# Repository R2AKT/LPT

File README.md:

License addendum - https://github.com/R2AKT/LPT/blob/main/Addendum.txt

# LPT

LPT (Centrinics) module. For Mega-80 (Mega-580) DIY 8-bit micro-computer - https://github.com/R2AKT/Mega-80.

Based on 82C11 (1834VV11).

Status: In production. Not tested.

Модуль LPT (Centrinics). Для самодельной 8-битной микро-ЭВМ - https://github.com/R2AKT/Mega-80.

На основе 1834ВВ11 (82C11).

Статус: Изготовливается. Не тестировалась.

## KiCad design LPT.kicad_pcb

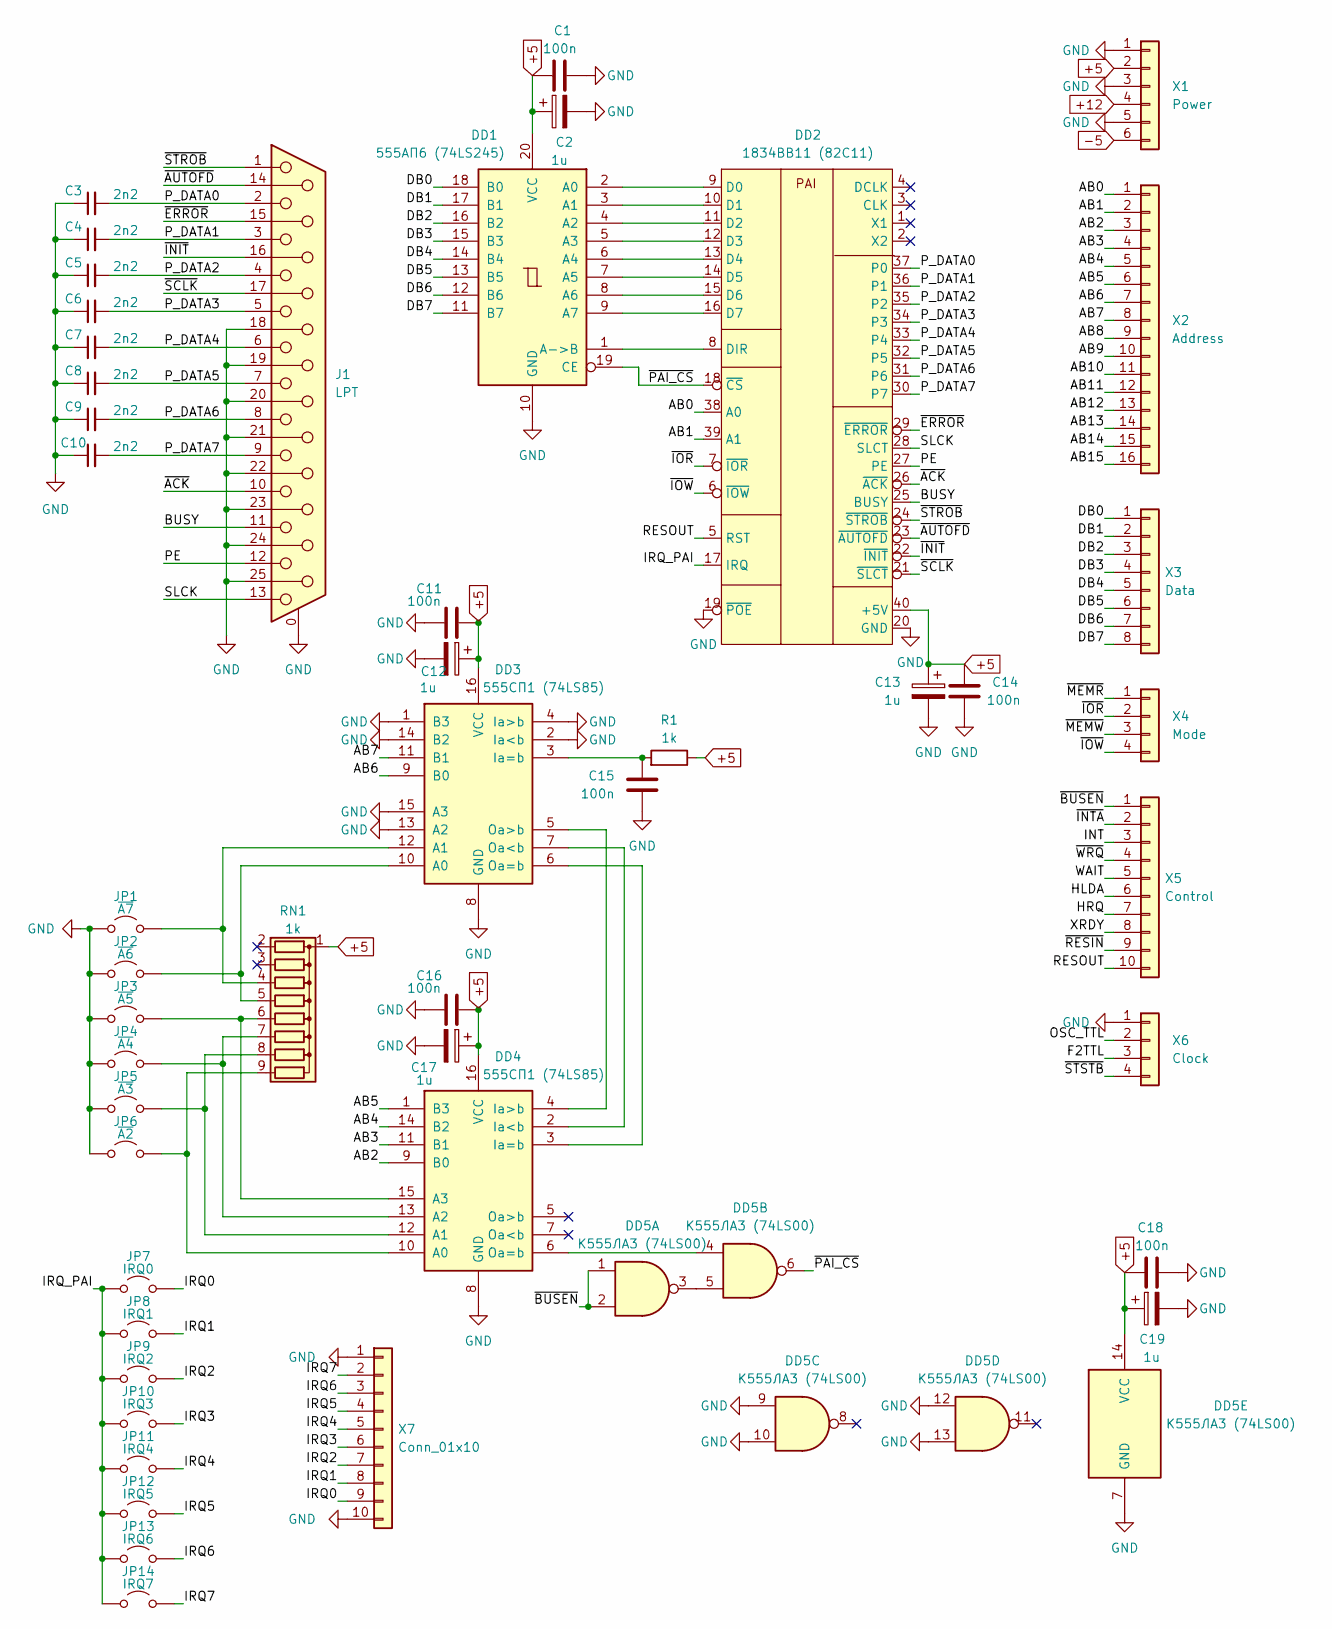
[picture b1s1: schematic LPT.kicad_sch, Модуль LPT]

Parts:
C1, C11, C14, C15, C16, C18: 100n; C_0805_2012Metric_Pad1.18x1.45mm_HandSolder
C2, C12, C13, C17, C19: 1u; CP_EIA-3216-18_Kemet-A_Pad1.58x1.35mm_HandSolder
C3, C4, C5, C6, C7, C8, C9, C10: 2n2; C_0805_2012Metric_Pad1.18x1.45mm_HandSolder
DD1: 555АП6 (74LS245); DIP-20_W7.62mm_Socket_LongPads
DD2: 1834ВВ11 (82C11); DIP-40_W15.24mm_Socket_LongPads
DD3, DD4: 555СП1 (74LS85); DIP-16_W7.62mm_Socket_LongPads
DD5: К555ЛА3 (74LS00); DIP-14_W7.62mm_Socket_LongPads
J1: LPT; DSUB-25_Female_Horizontal_P2.77x2.84mm_EdgePinOffset7.70mm_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
JP1: ~{A7}; SolderJumper-2_P1.3mm_Open_RoundedPad1.0x1.5mm
JP2: ~{A6}; SolderJumper-2_P1.3mm_Open_RoundedPad1.0x1.5mm
JP3: ~{A5}; SolderJumper-2_P1.3mm_Open_RoundedPad1.0x1.5mm
JP4: ~{A4}; SolderJumper-2_P1.3mm_Open_RoundedPad1.0x1.5mm
JP5: ~{A3}; SolderJumper-2_P1.3mm_Open_RoundedPad1.0x1.5mm
JP6: ~{A2}; SolderJumper-2_P1.3mm_Open_RoundedPad1.0x1.5mm
JP7: IRQ0; SolderJumper-2_P1.3mm_Open_RoundedPad1.0x1.5mm
JP8: IRQ1; SolderJumper-2_P1.3mm_Open_RoundedPad1.0x1.5mm
JP9: IRQ2; SolderJumper-2_P1.3mm_Open_RoundedPad1.0x1.5mm
JP10: IRQ3; SolderJumper-2_P1.3mm_Open_RoundedPad1.0x1.5mm
JP11: IRQ4; SolderJumper-2_P1.3mm_Open_RoundedPad1.0x1.5mm
JP12: IRQ5; SolderJumper-2_P1.3mm_Open_RoundedPad1.0x1.5mm
JP13: IRQ6; SolderJumper-2_P1.3mm_Open_RoundedPad1.0x1.5mm
JP14: IRQ7; SolderJumper-2_P1.3mm_Open_RoundedPad1.0x1.5mm
R1: 1k; R_0805_2012Metric_Pad1.20x1.40mm_HandSolder
RN1: 1k; R_Array_SIP9
X1: Power; PinHeader_1x06_P2.54mm_Vertical
X2: Address; PinHeader_1x16_P2.54mm_Vertical
X3: Data; PinHeader_1x08_P2.54mm_Vertical
X4: Mode; PinHeader_1x04_P2.54mm_Vertical
X5: Control; PinHeader_1x10_P2.54mm_Vertical
X6: Clock; PinHeader_1x04_P2.54mm_Vertical
X7: Conn_01x10; PinHeader_1x10_P2.54mm_Vertical

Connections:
+5: C1.1, C2.1, C11.1, C12.1, C13.1, C14.1, C16.1, C17.1, C18.1, C19.1, DD1.20 (VCC), DD2.40 (+5V), DD3.16 (VCC), DD4.16 (VCC), DD5.14 (VCC), R1.1, RN1.1 (common), X1.2
+12: X1.4
-5: X1.6
/AB0: DD2.38 (A0), X2.1
/AB1: DD2.39 (A1), X2.2
/AB2: DD4.9 (B0), X2.3
/AB3: DD4.11 (B1), X2.4
/AB4: DD4.14 (B2), X2.5
/AB5: DD4.1 (B3), X2.6
/AB6: DD3.9 (B0), X2.7
/AB7: DD3.11 (B1), X2.8
/AB8: X2.9
/AB9: X2.10
/AB10: X2.11
/AB11: X2.12
/AB12: X2.13
/AB13: X2.14
/AB14: X2.15
/AB15: X2.16
/BUSY: DD2.25 (BUSY), J1.11
/DB0: DD1.18 (B0), X3.1
/DB1: DD1.17 (B1), X3.2
/DB2: DD1.16 (B2), X3.3
/DB3: DD1.15 (B3), X3.4
/DB4: DD1.14 (B4), X3.5
/DB5: DD1.13 (B5), X3.6
/DB6: DD1.12 (B6), X3.7
/DB7: DD1.11 (B7), X3.8
/F2TTL: X6.3
/HLDA: X5.6
/HRQ: X5.7
/INT: X5.3
/IRQ0: JP7.2 (B), X7.9
/IRQ1: JP8.2 (B), X7.8
/IRQ2: JP9.2 (B), X7.7
/IRQ3: JP10.2 (B), X7.6
/IRQ4: JP11.2 (B), X7.5
/IRQ5: JP12.2 (B), X7.4
/IRQ6: JP13.2 (B), X7.3
/IRQ7: JP14.2 (B), X7.2
/IRQ_PAI: DD2.17 (IRQ), JP7.1 (A), JP8.1 (A), JP9.1 (A), JP10.1 (A), JP11.1 (A), JP12.1 (A), JP13.1 (A), JP14.1 (A)
/OSC_TTL: X6.2
/PE: DD2.27 (PE), J1.12
/P_DATA0: C3.2, DD2.37 (P0), J1.2
/P_DATA1: C4.2, DD2.36 (P1), J1.3
/P_DATA2: C5.2, DD2.35 (P2), J1.4
/P_DATA3: C6.2, DD2.34 (P3), J1.5
/P_DATA4: C7.2, DD2.33 (P4), J1.6
/P_DATA5: C8.2, DD2.32 (P5), J1.7
/P_DATA6: C9.2, DD2.31 (P6), J1.8
/P_DATA7: C10.2, DD2.30 (P7), J1.9
/RESOUT: DD2.5 (RST), X5.10
/SLCK: DD2.28 (SLCT), J1.13
/WAIT: X5.5
/XRDY: X5.8
/~ACK: DD2.26 (~ACK), J1.10
/~AUTOFD: DD2.23 (~AUTOFD), J1.14
/~BUSEN: DD5.1, DD5.2, X5.1
/~ERROR: DD2.29 (~ERROR), J1.15
/~INIT: DD2.22 (~INIT), J1.16
/~INTA: X5.2
/~IOR: DD2.7 (~IOR), X4.2
/~IOW: DD2.6 (~IOW), X4.4
/~MEMR: X4.1
/~MEMW: X4.3
/~PAI_CS: DD1.19 (CE), DD2.18 (~CS), DD5.6
/~RESIN: X5.9
/~SCLK: DD2.21 (~SLCT), J1.17
/~STROB: DD2.24 (~STROB), J1.1
/~STSTB: X6.4
/~WRQ: X5.4
GND: C1.2, C2.2, C3.1, C4.1, C5.1, C6.1, C7.1, C8.1, C9.1, C10.1, C11.2, C12.2, C13.2, C14.2, C15.2, C16.2, C17.2, C18.2, C19.2, DD1.10 (GND), DD2.19 (~POE), DD2.20 (GND), DD3.1 (B3), DD3.2 (Ia<b), DD3.4 (Ia>b), DD3.8 (GND), DD3.13 (A2), DD3.14 (B2), DD3.15 (A3), DD4.8 (GND), DD5.7 (GND), DD5.9, DD5.10, DD5.12, DD5.13, J1.0 (PAD), J1.18, J1.19, J1.20, J1.21, J1.22, J1.23, J1.24, J1.25, JP1.1 (A), JP2.1 (A), JP3.1 (A), JP4.1 (A), JP5.1 (A), JP6.1 (A), X1.1, X1.3, X1.5, X6.1, X7.1, X7.10
unnamed: DD1.2 (A0), DD2.9 (D0)
unnamed: DD1.3 (A1), DD2.10 (D1)
unnamed: DD1.4 (A2), DD2.11 (D2)
unnamed: DD1.5 (A3), DD2.12 (D3)
unnamed: DD1.6 (A4), DD2.13 (D4)
unnamed: DD1.7 (A5), DD2.14 (D5)
unnamed: DD1.8 (A6), DD2.15 (D6)
unnamed: DD1.9 (A7), DD2.16 (D7)
unnamed: DD1.1 (A->B), DD2.8 (DIR)
unnamed: DD3.10 (A0), JP2.2 (B), RN1.5 (R4)
unnamed: DD3.12 (A1), JP1.2 (B), RN1.4 (R3)
unnamed: C15.1, DD3.3 (Ia=b), R1.2
unnamed: DD3.7 (Oa<b), DD4.2 (Ia<b)
unnamed: DD3.6 (Oa=b), DD4.3 (Ia=b)
unnamed: DD3.5 (Oa>b), DD4.4 (Ia>b)
unnamed: DD4.10 (A0), JP6.2 (B), RN1.9 (R8)
unnamed: DD4.12 (A1), JP5.2 (B), RN1.8 (R7)
unnamed: DD4.13 (A2), JP4.2 (B), RN1.7 (R6)
unnamed: DD4.15 (A3), JP3.2 (B), RN1.6 (R5)
unnamed: DD4.6 (Oa=b), DD5.4
unnamed: DD5.3, DD5.5

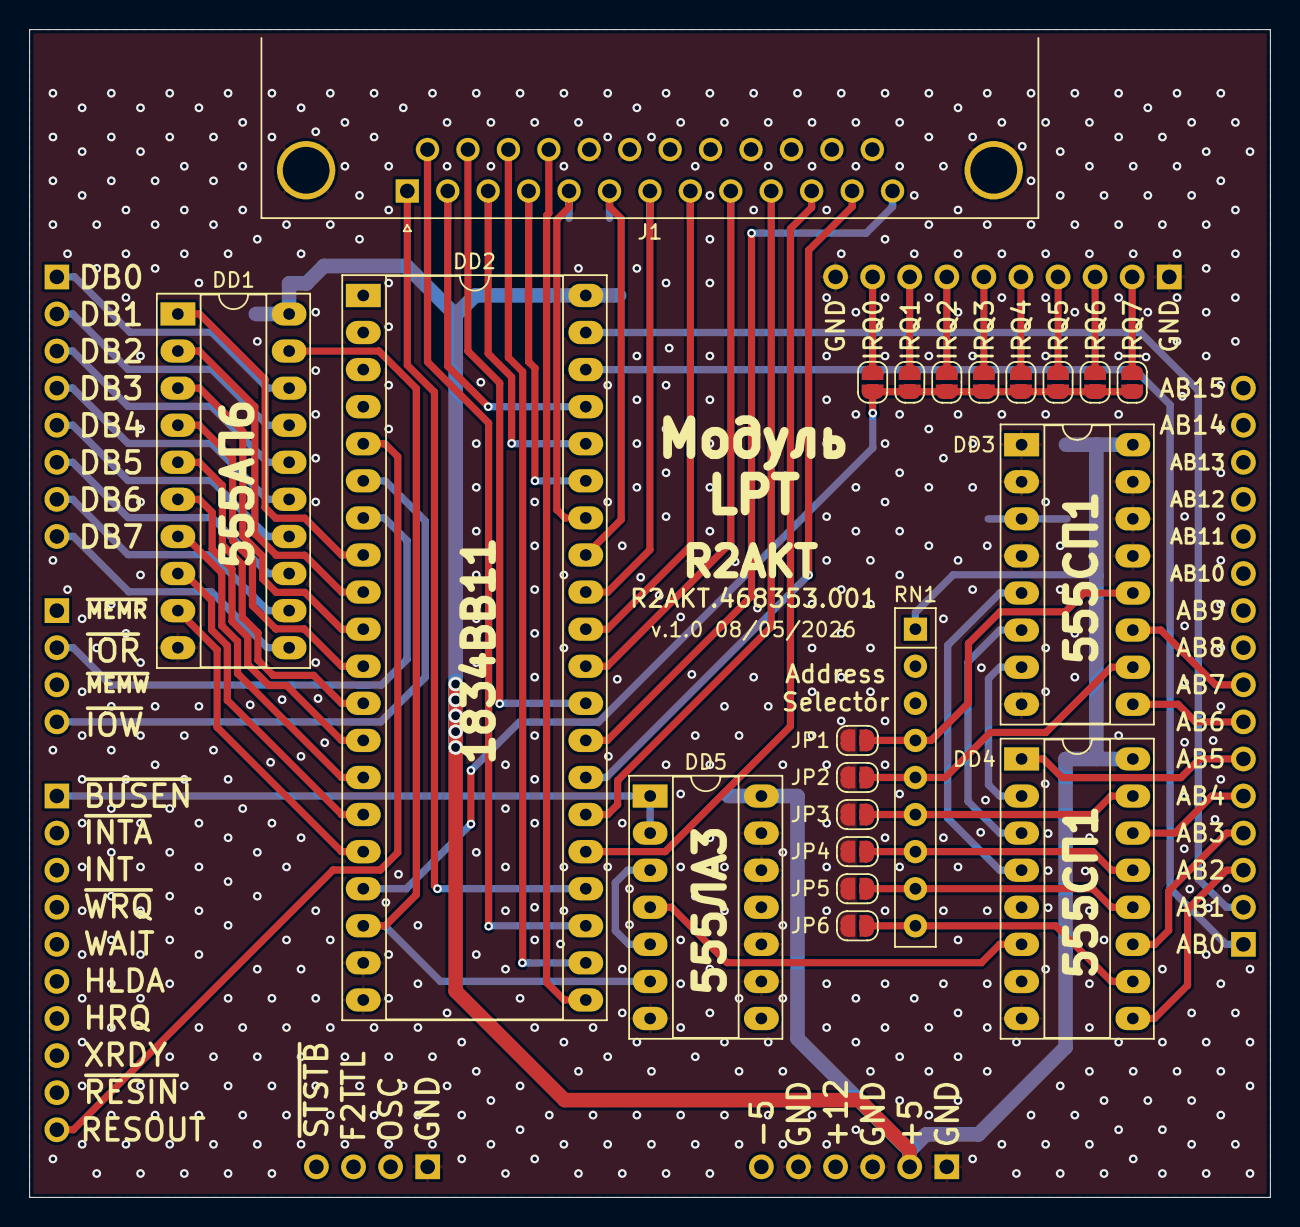
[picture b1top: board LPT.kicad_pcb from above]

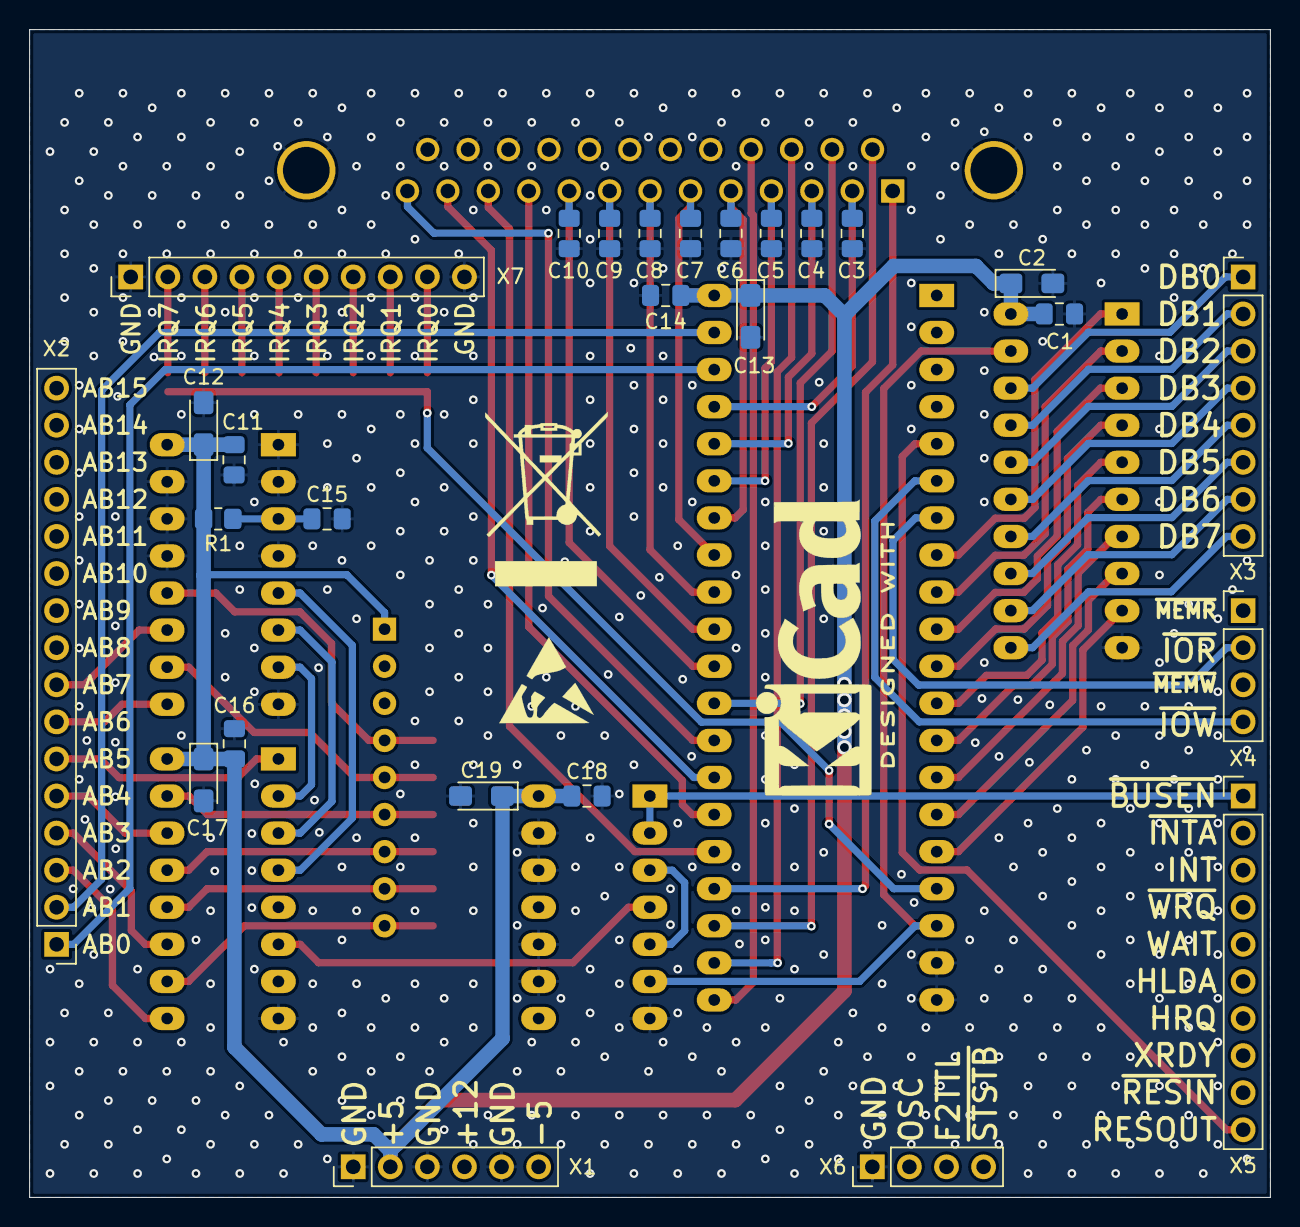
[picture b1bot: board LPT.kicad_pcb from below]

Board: 2 copper layers, 85.0 x 80.0 mm, 48 parts (27 on the bottom side), 70 nets.

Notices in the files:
README.md:
License: MIT
